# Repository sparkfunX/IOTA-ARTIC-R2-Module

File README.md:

# IOTA (Integrated Open-Source Transceiver for Argos)

[*SparkX IOTA (SPX-17984)*](https://www.sparkfun.com/products/17984)

The [ARGOS ARTIC R2 satellite communication chipset](https://www.cls-telemetry.com/argos-solutions/argos-products/modems/artic-chipset/#1534863095666-398318f3-c367) in castellated module format.

The ARTIC-R2 is an integrated low power small size ARGOS 2/3/4 single chip radio. ARTIC-R2 implements a message based wireless interface. For satellite uplink communication, ARTIC-R2 will encode, modulate and transmit provided user messages. For downlink communication, ARTIC-R2 will lock to the downstream, demodulate and decode it and extract the satellite messages.

The ARTIC-R2 can transmit signals in frequency bands around 400MHz and receive signals in the bands around 466MHz, in accordance with the ARGOS satellite system specifications. The ARTIC-R2 is compliant to all ARGOS 3 and ARGOS 4 RX and TX standards. It contains a RF transceiver and frequency synthesizer and a digital baseband modem. The ARTIC-R2 contains an on-chip power amplifier delivering 1mW [0dBm] output power, that serves as an output for connecting an external high efficient PA. The (de)modulation algorithms run on an on-chip DSP. This software approach allows for retargeting the ARTIC for other applications. The DSP program can be retained on an external flash or the MCU.

- Serial interface (SPI) for communication with MCU
- Programmable DSP core on board to ensure flexibility
- RX frequency : 466MHz – TX frequency: 400MHz
- Fractional N frequency synthesis
- Supported TX standards:
  - BPSK: PTT-A2 (ARGOS 2), PTT-VLD (ARGOS 4)
  - QPSK: PTT-A3, PTT-ZE (ARGOS 3)
  - GMSK: PTT-HD (ARGOS 3), PTT-MD (ARGOS 4), PTT-HD (ARGOS 4)
- Supported RX standards:
  - BPSK: PMT-A3 (ARGOS 3)
  - DSSS OQPSK: PMT-A4 (ARGOS 4) not available
- Dedicated flash Interface to retain Firmware
- Support COSPAS-SARSAT standard
- Operates on external 26MHz reference clock
- Dual supply, 1.8V and 3.3V
- Integrated PA (0dBm) to combine with external PA

An RFPA0133 programmable gain power amplifier boosts the 0dBm (1mW) output from the ARTIC by up to 26dB, producing a maximum transmit power level of 400mW. The transmit power can be adjusted via the **G8** pad.

The ARGOS satellite system is **currently** restricted to specific programs and applications. Please check that your project meets these requirements before buying hardware. [CLS (France)](https://www.cls-telemetry.com/argos-solutions/) and the [Woods Hole Group (America)](https://www.clsamerica.com/science-with-argos) will be able to advise if your project meets the requirements.
- _**"To meet system use requirements, all programs using Argos have to be related in some way or other to environmental protection, awareness or study, or to protecting human life."**_

## Repository Contents

- [**/Documents**](./Hardware) - Datasheets, test certificates, etc.
- [**/Hardware**](./Hardware) - Eagle PCB, SCH and LBR design files
- [**LICENSE.md**](./LICENSE.md) - contains the licence information

## Documentation

- [**Arduino Library**](https://github.com/sparkfun/SparkFun_ARGOS_ARTIC_R2_Arduino_Library) - SparkFun ARGOS ARTIC R2 Arduino Library
- [**Hookup Guide**](https://learn.sparkfun.com/tutorials/iota-artic-r2-satellite-communication-module-hookup-guide) - a hookup guide for the SparkFun IOTA - Satellite Communication Module (ARTIC R2)

## Thanks

The ARTIC R2 circuit is a remix of the reference design kindly provided by the [Arribada Initiative](https://arribada.org/) and Icoteq Ltd.

## License Information

This product is _**open source**_! 

Please review the LICENSE.md file for license information. 

If you have any questions or concerns on licensing, please contact technical support on our [SparkFun forums](https://forum.sparkfun.com/viewforum.php?f=152).

Distributed as-is; no warranty is given.

- Your friends at SparkFun.

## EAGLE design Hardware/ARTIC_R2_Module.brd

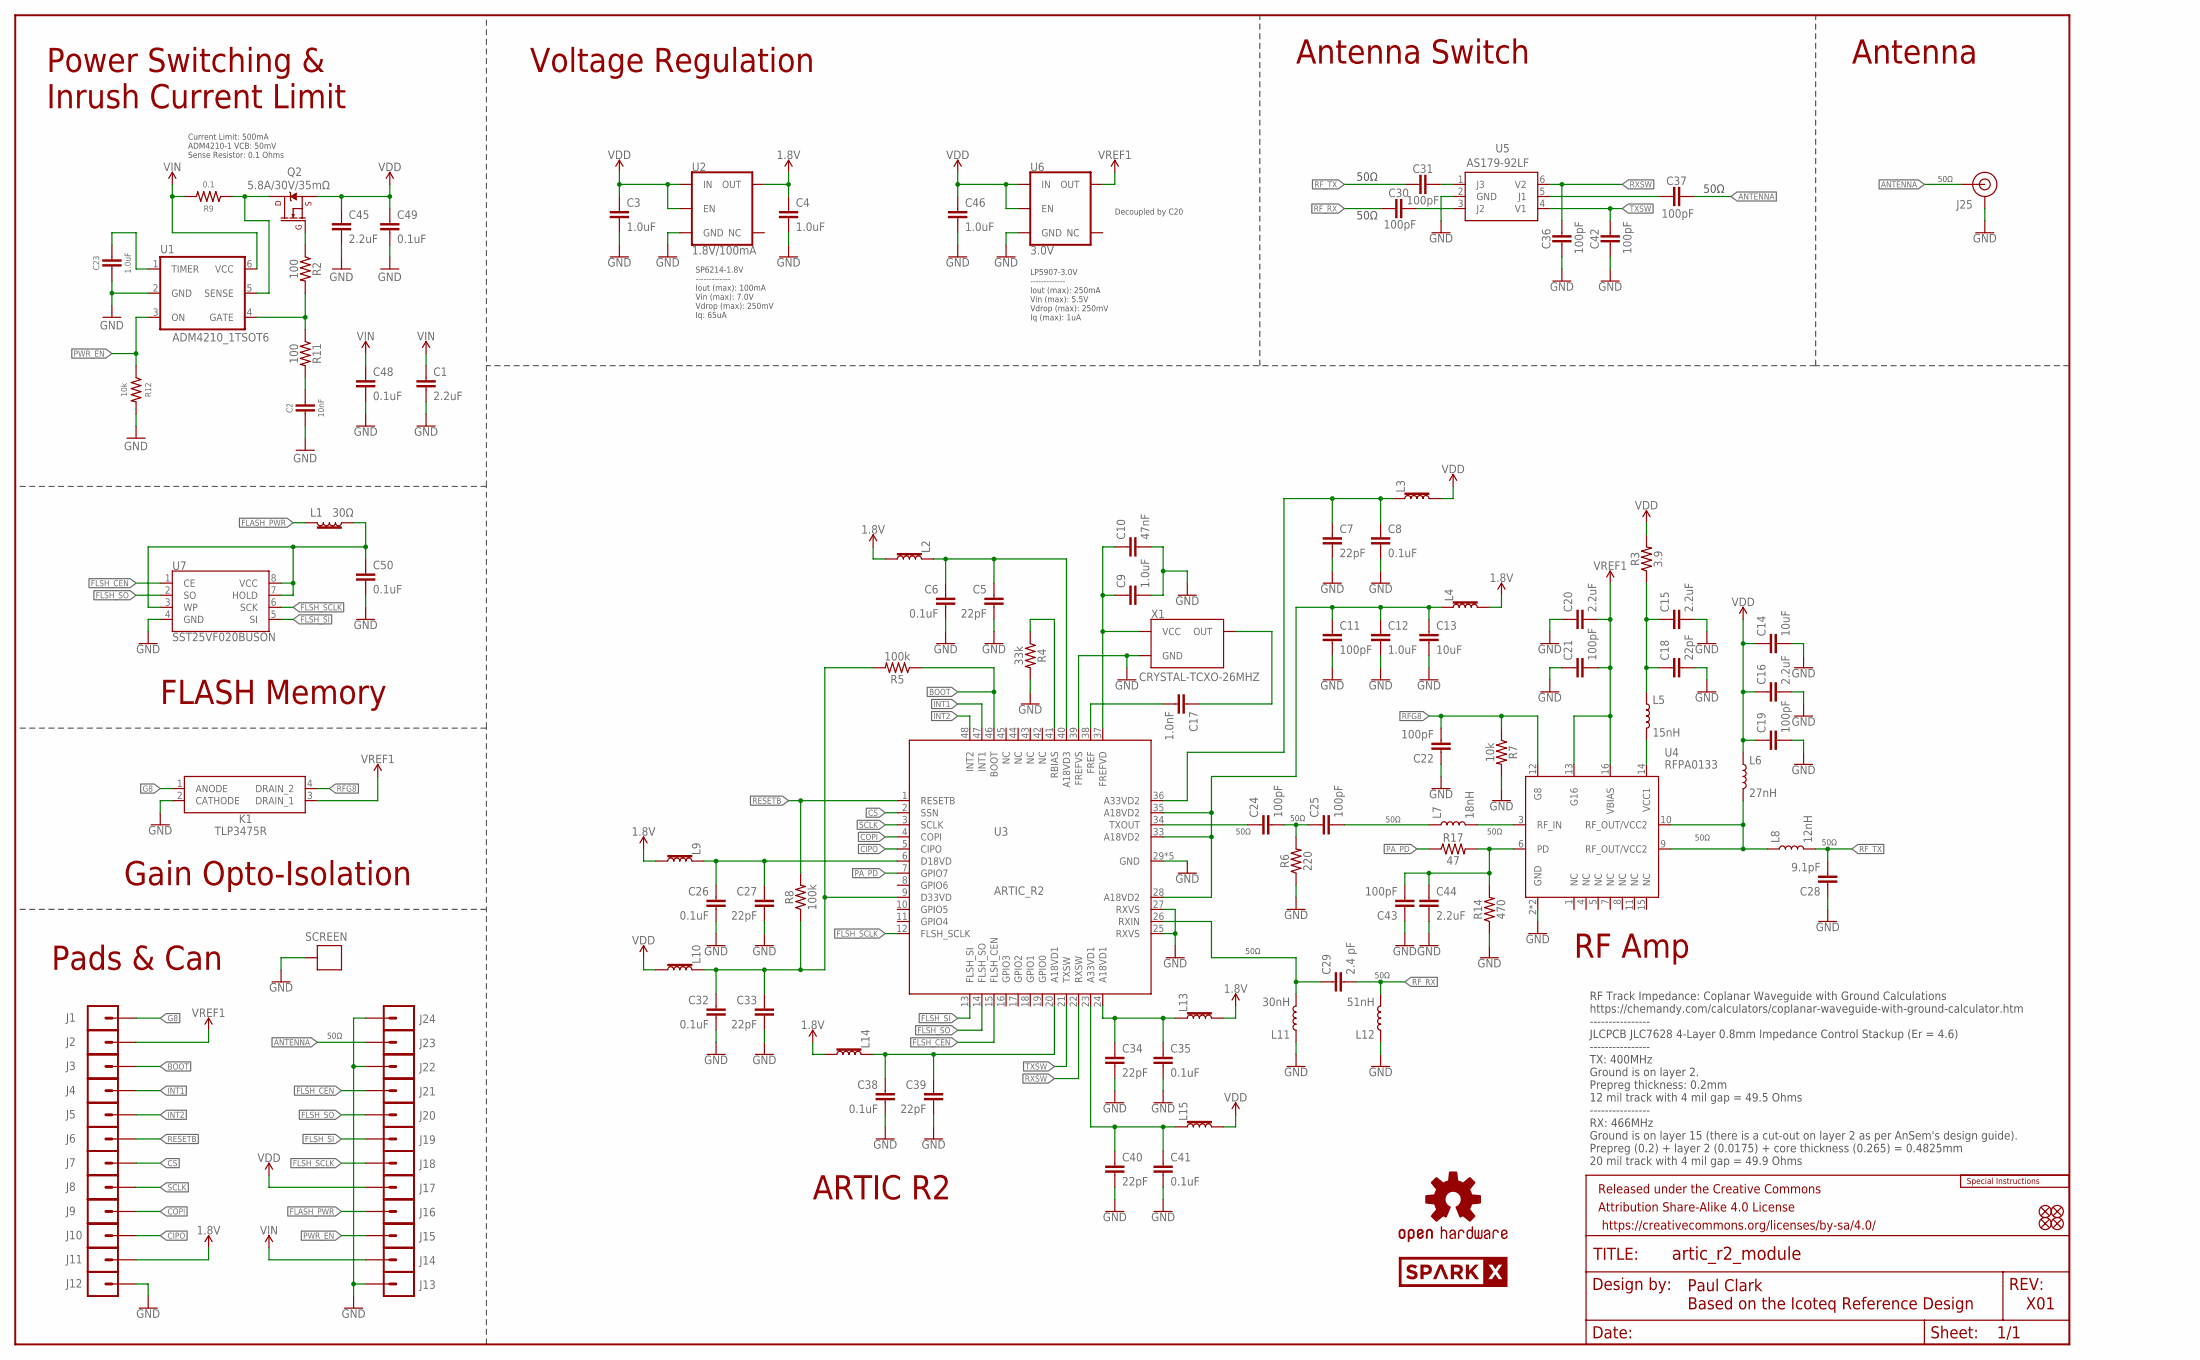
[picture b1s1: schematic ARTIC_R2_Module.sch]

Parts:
C1, C15, C16, C20, C44, C45: 2.2uF; 0402-TIGHT
C2: 10nF; 0402-TIGHT
C3, C4, C9, C12, C23, C46: 1.0uF; 0402-TIGHT
C5, C7, C18, C27, C33, C34, C39, C40: 22pF; 0402-TIGHT
C6, C8, C26, C32, C35, C38, C41, C48, C49, C50: 0.1uF; 0402-TIGHT
C10: 47nF; 0402-TIGHT
C11, C19, C21, C22, C24, C25, C30, C31, C36, C37, C42, C43: 100pF; 0402-TIGHT
C13, C14: 10uF; 0402-TIGHT
C17: 1.0nF; 0402-TIGHT
C28: 9.1pF; 0402-TIGHT
C29: 2.4 pF; 0402_MURATA
FD1, FD2, FD3, FD4: FIDUCIAL1X2; FIDUCIAL-1X2
FRAME1: FRAME-LEDGER; CREATIVE_COMMONS
J1, J2, J3, J4, J5, J6, J7, J8, J9, J10, J11, J12, J13, J14, J15, J16, J17, J18, J19, J20, J21, J22, J23, J24: CONN_01_CASTELLATED_4LAYERWITHOUT_VIA; CONN_01_CASTELLATED_4LAYER
J25: U.FL; U.FL_REDUCED_FOOTPRINT
K1: TLP3475R; TLP3475RTPF
L1, L2, L3, L4, L9, L10, L13, L14, L15: 30Ω; 0402-TIGHT
L5: 15nH; 0402_COILCRAFT
L6: 27nH; 0402_COILCRAFT
L7: 18nH; 0402_COILCRAFT
L8: 12nH; 0402_COILCRAFT
L11: 30nH; 0402_COILCRAFT
L12: 51nH; 0402_COILCRAFT
LOGO1: SPECIAL_INSTRUCTIONS-ORDERING; ORDERING_INSTRUCTIONS
LOGO3: OSHW-LOGOS; OSHW-LOGO-S
Q2: 5.8A/30V/35mΩ; SOT23-3
R2, R11: 100; 0402-TIGHT
R3: 3.9; 0402-TIGHT
R4: 33k; 0402-TIGHT
R5, R8: 100k; 0402-TIGHT
R6: 220; 0402-TIGHT
R7, R12: 10k; 0402-TIGHT
R9: 0.1; 0603
R14: 470; 0402-TIGHT
R17: 47; 0402-TIGHT
SCREEN: IOTA_SCREENING_CANSTRAIGHT_SLOTS; IOTA_CAN_STRAIGHT_SLOTS
SPARKX2: SPARKX-LOGO4; SPARKX-MEDIUM
U1: ADM4210_1TSOT6; TSOT6
U2: 1.8V/100mA; SC70
U3: ARTIC_R2; QFN-48
U4: RFPA0133; QFN50P300X300X86-17N
U5: AS179-92LF; SOT65P220X100-6N
U6: 3.0V; SOT23-5
U7: SST25VF020BUSON; USON_3X2MM
X1: CRYSTAL-TCXO-26MHZ; CRYSTAL-TCXO-SMD-1.65X1.25

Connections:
1.8V: C4.1, J11.1, L2.2, L4.2, L9.2, L13.2, L14.2, U2.5 (OUT)
ANTENNA: C37.1, J23.1, J25.FEED (SIGNAL)
BOOT: J3.1, R5.1, U3.46 (BOOT)
CIPO: J10.1, U3.5 (CIPO)
COPI: J9.1, U3.4 (COPI)
CS: J7.1, U3.2 (SSN)
FLASH_PWR: J16.1, L1.2
FLASH_VCC: C50.1, L1.1, U7.3 (WP), U7.7 (HOLD), U7.8 (VCC)
FLSH_CEN: J21.1, U3.15 (FLSH_CEN), U7.1 (CE)
FLSH_SCLK: J18.1, U3.12 (FLSH_SCLK), U7.6 (SCK)
FLSH_SI: J19.1, U3.13 (FLSH_SI), U7.5 (SI)
FLSH_SO: J20.1, U3.14 (FLSH_SO), U7.2 (SO)
G8: J1.1, K1.1 (ANODE)
GND: C1.2, C2.2, C3.2, C4.2, C5.2, C6.2, C7.2, C8.2, C9.2, C10.2, C11.2, C12.2, C13.2, C14.2, C15.2, C16.2, C18.2, C19.2, C20.1, C21.1, C22.1, C23.2, C26.2, C27.2, C28.1, C32.2, C33.2, C34.2, C35.2, C36.2, C38.2, C39.2, C40.2, C41.2, C42.2, C43.1, C44.2, C45.2, C46.2, C48.2, C49.2, C50.2, J12.1, J13.1, J22.1, J24.1, J25.1 (GND), J25.2 (GND), K1.2 (CATHODE), L11.P$1 (1), L12.P$1 (1), R4.2, R6.1, R7.2, R12.2, R14.1, SCREEN.1-1, SCREEN.1-16, SCREEN.2, SCREEN.3-1, SCREEN.3-16, SCREEN.4, U1.2 (GND), U2.2 (GND), U3.25 (RXVS), U3.27 (RXVS), U3.29 (GND), U3.30 (GND), U3.31 (GND), U3.32 (GND), U3.39 (FREFVS), U3.GND, U4.2 (GND), U4.EDAP (GND), U5.2 (GND), U6.2 (GND), U7.4 (GND), X1.1 (GND), X1.2 (GND)
INT1: J4.1, U3.47 (INT1)
INT2: J5.1, U3.48 (INT2)
unnamed: Q2.3 (D), R9.1, U1.5 (SENSE)
unnamed: Q2.1 (G), R2.1
unnamed: R2.2, R11.1, U1.4 (GATE)
unnamed: C34.1, C35.1, L13.1, U3.24 (A18VD1)
unnamed: C40.1, C41.1, L15.1, U3.23 (A33VD1)
unnamed: C2.1, R11.2
unnamed: C23.1, U1.1 (TIMER)
unnamed: C26.1, C27.1, L9.1, U3.6 (D18VD)
unnamed: C32.1, C33.1, L10.1, R5.2, R8.1, U3.9 (D33VD)
unnamed: C11.1, C12.1, C13.1, L4.1, U3.28 (A18VD2), U3.33 (A18VD2), U3.35 (A18VD2)
unnamed: C7.1, C8.1, L3.1, U3.36 (A33VD2)
unnamed: R4.1, U3.41 (RBIAS)
unnamed: C5.1, C6.1, L2.1, U3.40 (A18VD3)
unnamed: C9.1, C10.1, U3.37 (FREFVD), X1.4 (VCC)
unnamed: C17.1, X1.3 (OUT)
unnamed: C17.2, U3.38 (FREF)
unnamed: C24.1, U3.34 (TXOUT)
unnamed: C24.2, C25.1, R6.2
unnamed: L5.P$2 (2), U4.14 (VCC1)
unnamed: C15.1, C18.1, L5.P$1 (1), R3.1
unnamed: C29.P$1 (1), L11.P$2 (2), U3.26 (RXIN)
unnamed: C25.2, L7.P$1 (1)
unnamed: L7.P$2 (2), U4.3 (RF_IN)
unnamed: L6.P$2 (2), L8.P$1 (1), U4.9 (RF_OUT/VCC2), U4.10 (RF_OUT/VCC2)
unnamed: C31.1, U5.1 (J3)
unnamed: C30.1, U5.3 (J2)
unnamed: C37.2, U5.5 (J1)
unnamed: C38.1, C39.1, L14.1, U3.20 (A18VD1)
PA_PD: R17.1, U3.7 (GPIO7)
PD: C43.2, C44.1, R14.2, R17.2, U4.6 (PD)
PWR_EN: J15.1, R12.1, U1.3 (ON)
RESETB: J6.1, R8.2, U3.1 (RESETB)
RFG8: C22.2, K1.4 (DRAIN_2), R7.1, U4.12 (G8)
RF_RX: C29.P$2 (2), C30.2, L12.P$2 (2)
RF_TX: C28.2, C31.2, L8.P$2 (2)
RXSW: C36.1, U3.22 (RXSW), U5.6 (V2)
SCLK: J8.1, U3.3 (SCLK)
TXSW: C42.1, U3.21 (TXSW), U5.4 (V1)
VDD: C3.1, C14.1, C16.1, C19.1, C45.1, C46.1, C49.1, J17.1, L3.2, L6.P$1 (1), L10.2, L15.2, Q2.2 (S), R3.2, U2.1 (IN), U2.3 (EN), U6.1 (IN), U6.3 (EN)
VIN: C1.1, C48.1, J14.1, R9.2, U1.6 (VCC)
VREF1: C20.2, C21.2, J2.1, K1.3 (DRAIN_1), U4.13 (G16), U4.16 (VBIAS), U6.5 (OUT)

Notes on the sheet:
Paul Clark Based on the Icoteq Reference Design
X01
SP6214-1.8V ------------- Iout (max): 100mA Vin (max): 7.0V Vdrop (max): 250mV Iq: 65uA
Voltage Regulation
Antenna Switch
Antenna
ARTIC R2
RF Amp
Pads & Can
50Ω
RF Track Impedance: Coplanar Waveguide with Ground Calculations https://chemandy.com/calculators/coplanar-waveguide-with-ground-calculator.htm ---------------- JLCPCB JLC7628 4-Layer 0.8mm Impedance Control Stackup (Er = 4.6) ---------------- TX: 400MHz Ground is on layer 2. Prepreg thickness: 0.2m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
Gain Opto-Isolation
LP5907-3.0V ------------- Iout (max): 250mA Vin (max): 5.5V Vdrop (max): 250mV Iq (max): 1uA
Decoupled by C20
Power Switching & Inrush Current Limit
Current Limit: 500mA ADM4210-1 VCB: 50mV Sense Resistor: 0.1 Ohms
FLASH Memory

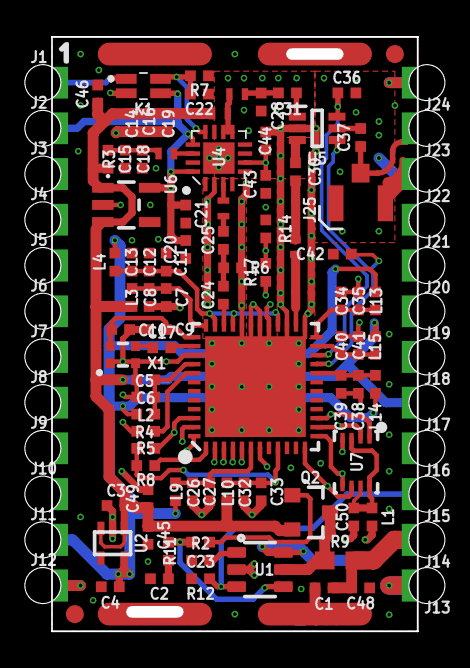
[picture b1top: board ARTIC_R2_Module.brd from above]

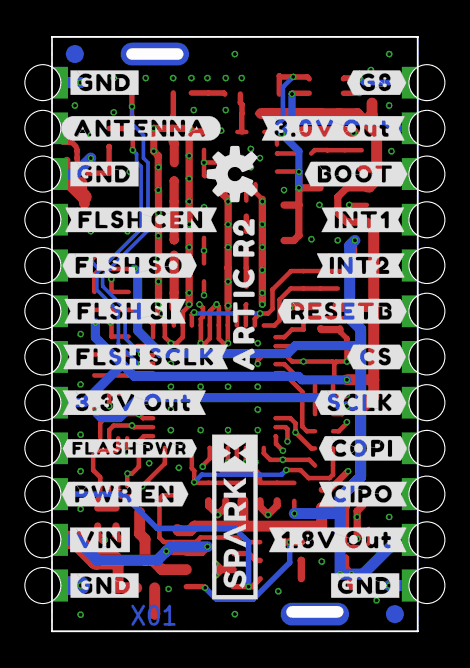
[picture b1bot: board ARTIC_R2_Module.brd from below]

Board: 4 copper layers, 20.3 x 33.0 mm, 146 parts (29 on the bottom side), 57 nets.

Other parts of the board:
U$1, U$3, U$4, U$5: #GND#0
U$2: 10
U$6: #PWR_EN#0
U$7: #VIN#0
U$8: #FLASH_PWR#0
U$9: #FLSH_SCLK#0
U$10: #FLSH_SI#0
U$11: #FLSH_SO#0
U$12: #FLSH_CEN#0
U$13: #3#3V_OUT#0
U$14: #ANTENNA#0
U$15: #G8#0
U$16: #3#0V_OUT#0
U$17: #BOOT#0
U$18: #INT1#0
U$19: #INT2#0
U$20: #RESETB#0
U$21: #CS#0
U$22: #SCLK#0
U$23: #COPI#0
U$24: #CIPO#0
U$25: #1#8V_OUT#0
U$26: ARTIC_R20

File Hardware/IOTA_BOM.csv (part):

"Part";"Value";"Device";"Package";"Description";"DESCRIPTION";"DESIGNER";"DIGIKEY_PART";"MANUFACTURER_NAME";"MANUFACTURER_PART";"MANUFACTURER_PART_NUMBER";"MANU_PART";"MOUSER_PART";"MOUSER_PART_NUMBER";"MOUSER_PRICE-STOCK";"PACKAGE";"PROD_ID";"REV";"VALUE";
"C1";"2.2uF";"2.2UF-0402_TIGHT-10V-10%-X5R";"0402-TIGHT";"2.2µF ceramic capacitors";"";"";"";"";"";"";"";"";"";"";"";"CAP-14232";"";"2.2uF";
"C2";"10nF";"10NF-0402T-25V-10%";"0402-TIGHT";"0.01uF/10nF/10,000pF ceramic capacitors";"";"";"";"";"";"";"";"";"";"";"";"CAP-14847";"";"10nF";
"C3";"1.0uF";"1.0UF-0402T-16V-10%";"0402-TIGHT";"1µF ceramic capacitors";"";"";"";"";"";"";"";"";"";"";"";"CAP-12417";"";"1.0uF";
"C4";"1.0uF";"1.0UF-0402T-16V-10%";"0402-TIGHT";"1µF ceramic capacitors";"";"";"";"";"";"";"";"";"";"";"";"CAP-12417";"";"1.0uF";
"C5";"22pF";"22PF-0402T-16V-10%";"0402-TIGHT";"22pF ceramic capacitors";"";"";"";"";"";"";"";"";"";"";"";"CAP-14674";"";"22pF";
"C6";"0.1uF";"0.1UF-0402T-6.3V-10%-X7R";"0402-TIGHT";"0.1µF ceramic capacitors";"";"";"";"";"";"";"";"";"";"";"";"CAP-14993";"";"0.1uF";
"C7";"22pF";"22PF-0402T-16V-10%";"0402-TIGHT";"22pF ceramic capacitors";"";"";"";"";"";"";"";"";"";"";"";"CAP-14674";"";"22pF";
"C8";"0.1uF";"0.1UF-0402T-6.3V-10%-X7R";"0402-TIGHT";"0.1µF ceramic capacitors";"";"";"";"";"";"";"";"";"";"";"";"CAP-14993";"";"0.1uF";
"C9";"1.0uF";"1.0UF-0402T-16V-10%";"0402-TIGHT";"1µF ceramic capacitors";"";"";"";"";"";"";"";"";"";"";"";"CAP-12417";"";"1.0uF";
"C10";"47nF";"47NF-0402_TIGHT-25V-10%-X7R";"0402-TIGHT";"47nF ceramic capacitors";"";"";"";"";"";"";"";"";"";"";"";"CAP-14243";"";"47nF";
"C11";"100pF";"100PF-0402T-50V-5%";"0402-TIGHT";"100pF/0.1nF ceramic capacitors";"";"";"";"";"";"";"";"";"";"";"";"CAP-13458";"";"100pF";
"C12";"1.0uF";"1.0UF-0402T-16V-10%";"0402-TIGHT";"1µF ceramic capacitors";"";"";"";"";"";"";"";"";"";"";"";"CAP-12417";"";"1.0uF";
"C13";"10uF";"10UF-0402T-6.3V-20%";"0402-TIGHT";"10.0µF ceramic capacitors";"";"";"";"";"";"";"";"";"";"";"";"CAP-14848";"";"10uF";
"C14";"10uF";"10UF-0402T-6.3V-20%";"0402-TIGHT";"10.0µF ceramic capacitors";"";"";"";"";"";"";"";"";"";"";"";"CAP-14848";"";"10uF";
"C15";"2.2uF";"2.2UF-0402_TIGHT-10V-10%-X5R";"0402-TIGHT";"2.2µF ceramic capacitors";"";"";"";"";"";"";"";"";"";"";"";"CAP-14232";"";"2.2uF";
"C16";"2.2uF";"2.2UF-0402_TIGHT-10V-10%-X5R";"0402-TIGHT";"2.2µF ceramic capacitors";"";"";"";"";"";"";"";"";"";"";"";"CAP-14232";"";"2.2uF";
"C17";"1.0nF";"1.0NF/1000PF-0402_TIGHT-50V-10%";"0402-TIGHT";"1nF/1,000pF ceramic capacitors";"";"";"";"";"";"";"";"";"";"";"";"CAP-14280";"";"1.0nF";
"C18";"22pF";"22PF-0402T-16V-10%";"0402-TIGHT";"22pF ceramic capacitors";"";"";"";"";"";"";"";"";"";"";"";"CAP-14674";"";"22pF";
"C19";"100pF";"100PF-0402T-50V-5%";"0402-TIGHT";"100pF/0.1nF ceramic capacitors";"";"";"";"";"";"";"";"";"";"";"";"CAP-13458";"";"100pF";
"C20";"2.2uF";"2.2UF-0402_TIGHT-10V-10%-X5R";"0402-TIGHT";"2.2µF ceramic capacitors";"";"";"";"";"";"";"";"";"";"";"";"CAP-14232";"";"2.2uF";
"C21";"100pF";"100PF-0402T-50V-5%";"0402-TIGHT";"100pF/0.1nF ceramic capacitors";"";"";"";"";"";"";"";"";"";"";"";"CAP-13458";"";"100pF";
"C22";"100pF";"100PF-0402T-50V-5%";"0402-TIGHT";"100pF/0.1nF ceramic capacitors";"";"";"";"";"";"";"";"";"";"";"";"CAP-13458";"";"100pF";
"C23";"1.0uF";"1.0UF-0402T-16V-10%";"0402-TIGHT";"1µF ceramic capacitors";"";"";"";"";"";"";"";"";"";"";"";"CAP-12417";"";"1.0uF";
"C24";"100pF";"100PF-0402T-50V-5%";"0402-TIGHT";"100pF/0.1nF ceramic capacitors";"";"";"";"";"";"";"";"";"";"";"";"CAP-13458";"";"100pF";
"C25";"100pF";"100PF-0402T-50V-5%";"0402-TIGHT";"100pF/0.1nF ceramic capacitors";"";"";"";"";"";"";"";"";"";"";"";"CAP-13458";"";"100pF";
"C26";"0.1uF";"0.1UF-0402T-6.3V-10%-X7R";"0402-TIGHT";"0.1µF ceramic capacitors";"";"";"";"";"";"";"";"";"";"";"";"CAP-14993";"";"0.1uF";
"C27";"22pF";"22PF-0402T-16V-10%";"0402-TIGHT";"22pF ceramic capacitors";"";"";"";"";"";"";"";"";"";"";"";"CAP-14674";"";"22pF";
"C28";"9.1pF";"9.1PF-0402-TIGHT";"0402-TIGHT";"9.1pF ceramic capacitors";"";"";"";"";"";"";"";"609-500R07S9R1CV4T";"";"";"";"CAP-15278";"";"9.1pF";
"C29";"2.4 pF";"2.4PF-0402";"0402_MURATA";"";"";"";"";"";"";"";"";"";"";"";"";"CAP-14351";"";"2.4 pF";
"C30";"100pF";"100PF-0402T-50V-5%";"0402-TIGHT";"100pF/0.1nF ceramic capacitors";"";"";"";"";"";"";"";"";"";"";"";"CAP-13458";"";"100pF";
"C31";"100pF";"100PF-0402T-50V-5%";"0402-TIGHT";"100pF/0.1nF ceramic capacitors";"";"";"";"";"";"";"";"";"";"";"";"CAP-13458";"";"100pF";
"C32";"0.1uF";"0.1UF-0402T-6.3V-10%-X7R";"0402-TIGHT";"0.1µF ceramic capacitors";"";"";"";"";"";"";"";"";"";"";"";"CAP-14993";"";"0.1uF";
"C33";"22pF";"22PF-0402T-16V-10%";"0402-TIGHT";"22pF ceramic capacitors";"";"";"";"";"";"";"";"";"";"";"";"CAP-14674";"";"22pF";
"C34";"22pF";"22PF-0402T-16V-10%";"0402-TIGHT";"22pF ceramic capacitors";"";"";"";"";"";"";"";"";"";"";"";"CAP-14674";"";"22pF";
"C35";"0.1uF";"0.1UF-0402T-6.3V-10%-X7R";"0402-TIGHT";"0.1µF ceramic capacitors";"";"";"";"";"";"";"";"";"";"";"";"CAP-14993";"";"0.1uF";
"C36";"100pF";"100PF-0402T-50V-5%";"0402-TIGHT";"100pF/0.1nF ceramic capacitors";"";"";"";"";"";"";"";"";"";"";"";"CAP-13458";"";"100pF";
"C37";"100pF";"100PF-0402T-50V-5%";"0402-TIGHT";"100pF/0.1nF ceramic capacitors";"";"";"";"";"";"";"";"";"";"";"";"CAP-13458";"";"100pF";
"C38";"0.1uF";"0.1UF-0402T-6.3V-10%-X7R";"0402-TIGHT";"0.1µF ceramic capacitors";"";"";"";"";"";"";"";"";"";"";"";"CAP-14993";"";"0.1uF";
"C39";"22pF";"22PF-0402T-16V-10%";"0402-TIGHT";"22pF ceramic capacitors";"";"";"";"";"";"";"";"";"";"";"";"CAP-14674";"";"22pF";
"C40";"22pF";"22PF-0402T-16V-10%";"0402-TIGHT";"22pF ceramic capacitors";"";"";"";"";"";"";"";"";"";"";"";"CAP-14674";"";"22pF";
"C41";"0.1uF";"0.1UF-0402T-6.3V-10%-X7R";"0402-TIGHT";"0.1µF ceramic capacitors";"";"";"";"";"";"";"";"";"";"";"";"CAP-14993";"";"0.1uF";
"C42";"100pF";"100PF-0402T-50V-5%";"0402-TIGHT";"100pF/0.1nF ceramic capacitors";"";"";"";"";"";"";"";"";"";"";"";"CAP-13458";"";"100pF";
"C43";"100pF";"100PF-0402T-50V-5%";"0402-TIGHT";"100pF/0.1nF ceramic capacitors";"";"";"";"";"";"";"";"";"";"";"";"CAP-13458";"";"100pF";
"C44";"2.2uF";"2.2UF-0402_TIGHT-10V-10%-X5R";"0402-TIGHT";"2.2µF ceramic capacitors";"";"";"";"";"";"";"";"";"";"";"";"CAP-14232";"";"2.2uF";
"C45";"2.2uF";"2.2UF-0402_TIGHT-10V-10%-X5R";"0402-TIGHT";"2.2µF ceramic capacitors";"";"";"";"";"";"";"";"";"";"";"";"CAP-14232";"";"2.2uF";
"C46";"1.0uF";"1.0UF-0402T-16V-10%";"0402-TIGHT";"1µF ceramic capacitors";"";"";"";"";"";"";"";"";"";"";"";"CAP-12417";"";"1.0uF";
"C48";"0.1uF";"0.1UF-0402T-10V-10%-X7R";"0402-TIGHT";"0.1µF ceramic capacitors";"";"";"";"";"";"";"";"";"";"";"";"CAP-15083";"";"0.1uF";
"C49";"0.1uF";"0.1UF-0402T-10V-10%-X7R";"0402-TIGHT";"0.1µF ceramic capacitors";"";"";"";"";"";"";"";"";"";"";"";"CAP-15083";"";"0.1uF";
"C50";"0.1uF";"0.1UF-0402T-6.3V-10%-X7R";"0402-TIGHT";"0.1µF ceramic capacitors";"";"";"";"";"";"";"";"";"";"";"";"CAP-14993";"";"0.1uF";
"FD1";"FIDUCIAL1X2";"FIDUCIAL1X2";"FIDUCIAL-1X2";"Fiducial Alignment Points";"";"";"";"";"";"";"";"";"";"";"";"";"";"";
"FD2";"FIDUCIAL1X2";"FIDUCIAL1X2";"FIDUCIAL-1X2";"Fiducial Alignment Points";"";"";"";"";"";"";"";"";"";"";"";"";"";"";
"FD3";"FIDUCIAL1X2";"FIDUCIAL1X2";"FIDUCIAL-1X2";"Fiducial Alignment Points";"";"";"";"";"";"";"";"";"";"";"";"";"";"";
"FD4";"FIDUCIAL1X2";"FIDUCIAL1X2";"FIDUCIAL-1X2";"Fiducial Alignment Points";"";"";"";"";"";"";"";"";"";"";"";"";"";"";
"FRAME1";"FRAME-LEDGER";"FRAME-LEDGER";"CREATIVE_COMMONS";"Schematic Frame - Ledger";"";"";"";"";"";"";"";"";"";"";"";"";"";"";
"J1";"";"CONN_01_CASTELLATED_4LAYERWITHOUT_VIA";"CONN_01_CASTELLATED_4LAYER";"A castellated pad for 4-layer boards.";"";"";"";"";"";"";"";"";"";"";"";"";"";"";
"J2";"";"CONN_01_CASTELLATED_4LAYERWITHOUT_VIA";"CONN_01_CASTELLATED_4LAYER";"A castellated pad for 4-layer boards.";"";"";"";"";"";"";"";"";"";"";"";"";"";"";
"J3";"";"CONN_01_CASTELLATED_4LAYERWITHOUT_VIA";"CONN_01_CASTELLATED_4LAYER";"A castellated pad for 4-layer boards.";"";"";"";"";"";"";"";"";"";"";"";"";"";"";
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
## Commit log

2020-12-14 Work in progress
2020-12-15 Adding panel files. Updating README.
2020-12-15 Adding 50Ohms to the Antenna Pad
2020-12-16 Adding better castellated pads. Correcting cutouts for screen tabs.
2020-12-18 Updated the screening can
2020-12-18 Moved the X01 to make it visible
2021-01-12 Added the flash memory in USON format
    The flash has its own power pin so it can be programmed independantly - without needing the ARTIC to be powered up and held in reset. The user will need to jump the flash power pad across to the adja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
2021-01-12 Update README with revised pad names
2021-01-19 Adding missing PROD_IDs. Changed pad metal on layers 2 & 15 to polygons instead of rectangles (got rid of some errors).
2021-01-21 Changed name to IOTA
2021-02-04 Adding a note of the SKU
2021-04-26 Add the documents
2021-09-07 Add BOM
2021-10-28 Add product image
2021-11-22 Update README - add link to the Hookup Guide
2021-11-22 Update Eagle files - remove New_Parts libraries

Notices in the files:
parts and their libraries:
SparkFun-Aesthetics: Licensing: Creative Commons ShareAlike 4.0 International - https://creativecommons.org/licenses/by-sa/4.0
SparkFun-Aesthetics: Released under the Creative Commons Attribution Share-Alike 4.0 License
SparkFun-Aesthetics: https://creativecommons.org/licenses/by-sa/4.0
